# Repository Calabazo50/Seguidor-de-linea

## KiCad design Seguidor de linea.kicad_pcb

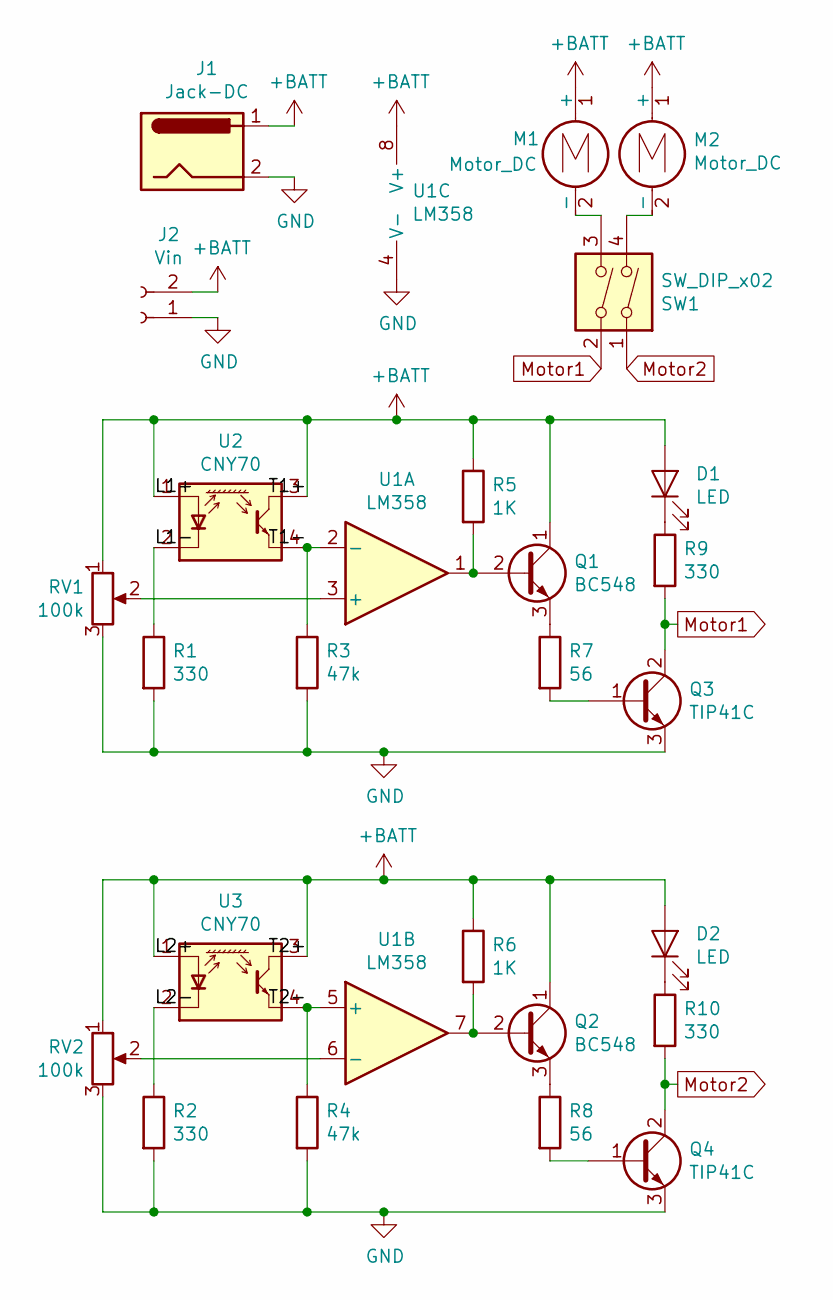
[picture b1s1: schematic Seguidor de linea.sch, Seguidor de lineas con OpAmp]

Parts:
D1, D2: LED; LED_D5.0mm
J1: Jack-DC; BarrelJack_Horizontal
J2: Vin; PinSocket_1x02_P2.54mm_Vertical
M1, M2: Motor_DC; TerminalBlock_bornier-2_P5.08mm
Q1, Q2: BC548; TO-92_Inline_Wide
Q3, Q4: TIP41C; TO-220-3_Vertical
R1, R2, R9, R10: 330; R_Axial_DIN0207_L6.3mm_D2.5mm_P10.16mm_Horizontal
R3, R4: 47k; R_Axial_DIN0207_L6.3mm_D2.5mm_P10.16mm_Horizontal
R5, R6: 1K; R_Axial_DIN0207_L6.3mm_D2.5mm_P10.16mm_Horizontal
R7, R8: 56; R_Axial_DIN0207_L6.3mm_D2.5mm_P10.16mm_Horizontal
RV1, RV2: 100k; Potentiometer_Alps_RK163_Single_Horizontal
SW1: SW_DIP_x02; SW_DIP_SPSTx02_Slide_9.78x7.26mm_W7.62mm_P2.54mm
U1: LM358; DIP-8_W7.62mm_Socket_LongPads
U2, U3: CNY70; PinSocket_1x04_P2.54mm_Vertical

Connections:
+BATT: D1.2 (A), D2.2 (A), J1.1, J2.2, M1.1 (+), M2.1 (+), Q1.1 (C), Q2.1 (C), R5.1, R6.1, RV1.1, RV2.1, U1.8 (V+), U2.1 (A), U2.3 (C), U3.1 (A), U3.3 (C)
/L1-: R1.1, U2.2 (K)
/L2-: R2.1, U3.2 (K)
/T1-: R3.1, U1.2 (-), U2.4 (E)
/T2-: R4.1, U1.5 (+), U3.4 (E)
GND: J1.2, J2.1, Q3.3 (E), Q4.3 (E), R1.2, R2.2, R3.2, R4.2, RV1.3, RV2.3, U1.4 (V-)
Motor1: Q3.2 (C), R9.2, SW1.2
Motor2: Q4.2 (C), R10.2, SW1.1
unnamed: D1.1 (K), R9.1
unnamed: D2.1 (K), R10.1
unnamed: M1.2 (-), SW1.3
unnamed: M2.2 (-), SW1.4
unnamed: Q1.2 (B), R5.2, U1.1
unnamed: Q1.3 (E), R7.1
unnamed: Q2.2 (B), R6.2, U1.7
unnamed: Q2.3 (E), R8.1
unnamed: Q3.1 (B), R7.2
unnamed: Q4.1 (B), R8.2
unnamed: RV1.2, U1.3 (+)
unnamed: RV2.2, U1.6 (-)

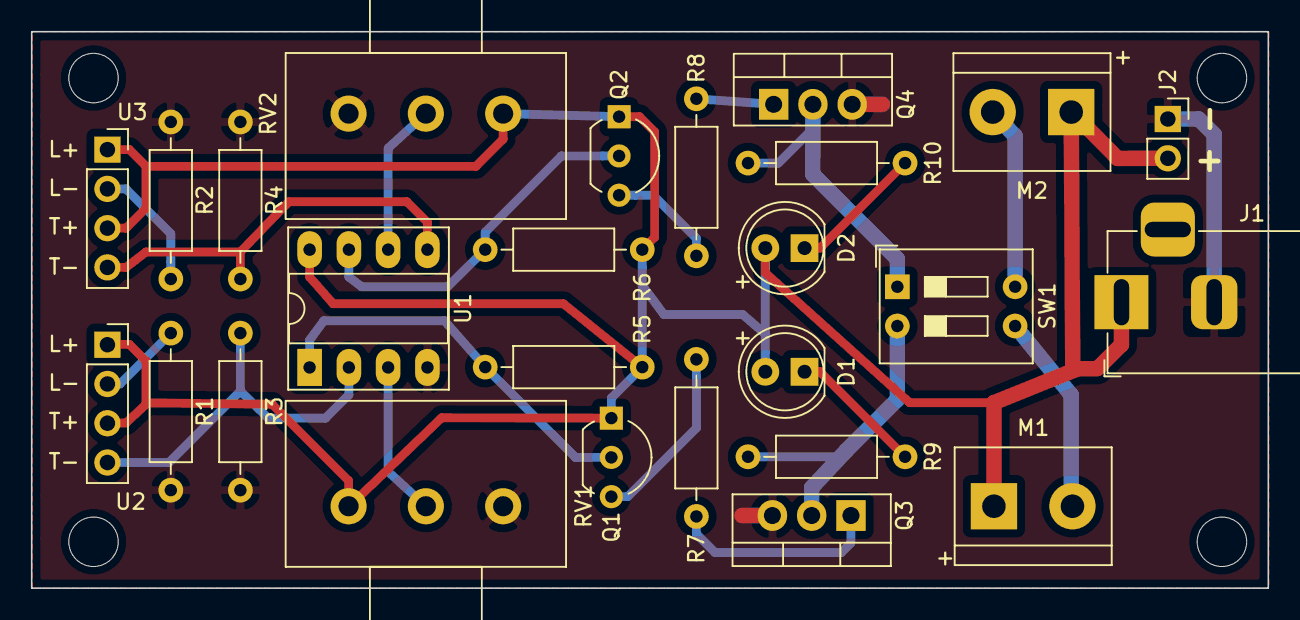
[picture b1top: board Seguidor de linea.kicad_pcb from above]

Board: 2 copper layers, 80.0 x 36.0 mm, 26 parts (0 on the bottom side), 20 nets.

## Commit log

2021-08-22 Versión final del seguidor terminada
